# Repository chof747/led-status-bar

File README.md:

## Status bar with RGB Leds

This is a breakout board containing 5 WS2812B compatible RGB Leds that can be used to display some kind of status information or for other presentation stuff

It contains the following elements:

- 5 WS2812B compatible surface mount RGB leds
- MOSFETs acting as signal level shifters so it can be triggered by a 3V3 signal while the LEDs are powered by a higher voltage
- By-pass capacitors for each LED according to the data sheets
- A 4-pin header so that it can be connected to VDD (e.g. 5V) and VREF (e.g. 3v3), GND and a data line
  (1 - VDD, 2- Data, 3 - VREF, 4 - GND)
- It contains an outbound connector to daisy chain boards

## Revision History:

- **v1.0**: Initial version (filed for fabrication: 19.04.2023, assembled 14.5.2023)
- **v1.1**: Corrected revision including fixed version for level shifting and an outbound connector

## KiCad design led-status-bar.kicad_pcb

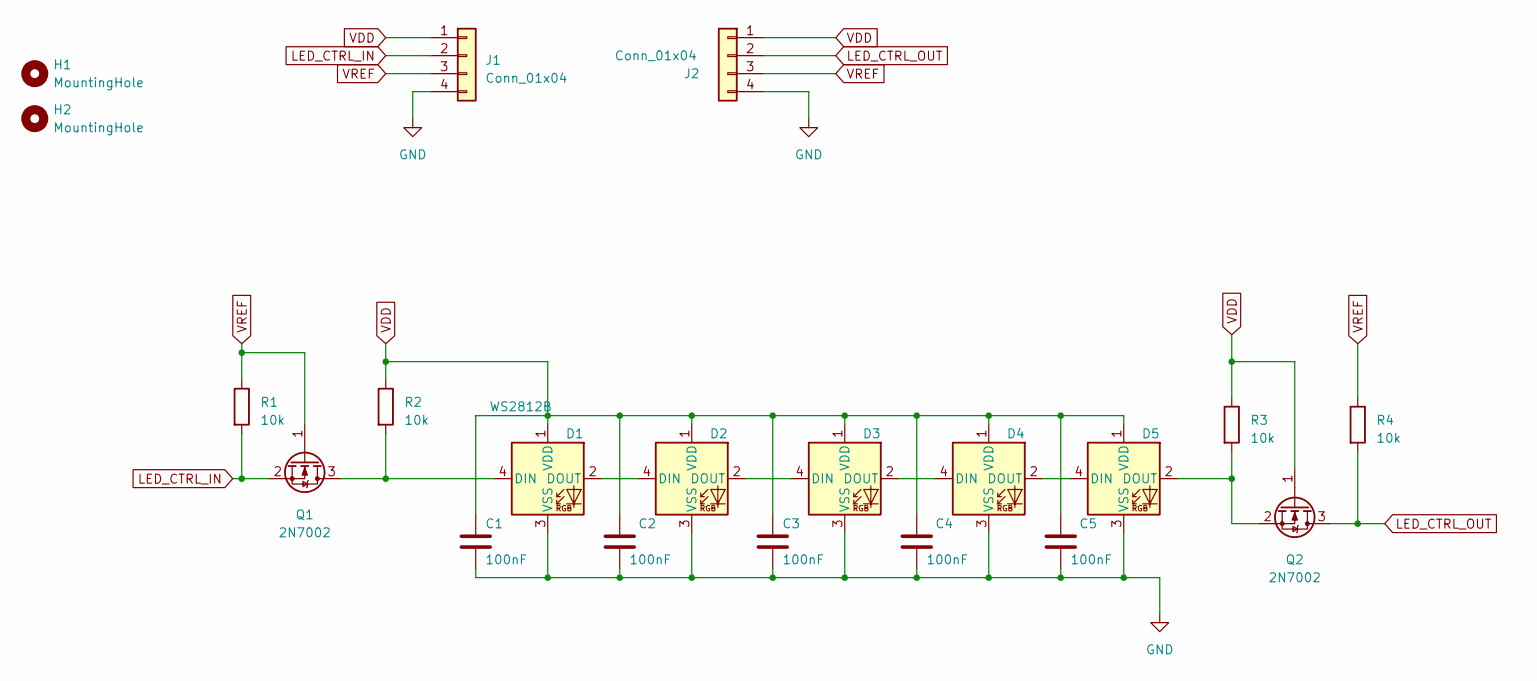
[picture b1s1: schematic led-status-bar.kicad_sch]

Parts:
C1, C2, C3, C4, C5: 100nF; C_0603_1608Metric_Pad1.08x0.95mm_HandSolder
D1, D2, D3, D4, D5: WS2812B; LED_WS2812B_PLCC4_5.0x5.0mm_P3.2mm
H1, H2: MountingHole; MountingHole_3.2mm_M3-smallBorder
J1: Conn_01x04; PinHeader_1x04_P2.54mm_Horizontal
J2: Conn_01x04; PinSocket_1x04_P2.54mm_Horizontal
Q1, Q2: 2N7002; SOT-23
R1, R2, R3, R4: 10k; R_0603_1608Metric_Pad0.98x0.95mm_HandSolder

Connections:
GND: C1.2, C2.2, C3.2, C4.2, C5.2, D1.3 (VSS), D2.3 (VSS), D3.3 (VSS), D4.3 (VSS), D5.3 (VSS), J1.4, J2.4
LED_CTRL_IN: J1.2, Q1.2 (S), R1.2
LED_CTRL_OUT: J2.2, Q2.3 (D), R4.2
unnamed: D1.4 (DIN), Q1.3 (D), R2.2
unnamed: D1.2 (DOUT), D2.4 (DIN)
unnamed: D2.2 (DOUT), D3.4 (DIN)
unnamed: D3.2 (DOUT), D4.4 (DIN)
unnamed: D4.2 (DOUT), D5.4 (DIN)
unnamed: D5.2 (DOUT), Q2.2 (S), R3.2
VDD: C1.1, C2.1, C3.1, C4.1, C5.1, D1.1 (VDD), D2.1 (VDD), D3.1 (VDD), D4.1 (VDD), D5.1 (VDD), J1.1, J2.1, Q2.1 (G), R2.1, R3.1
VREF: J1.3, J2.3, Q1.1 (G), R1.1, R4.1

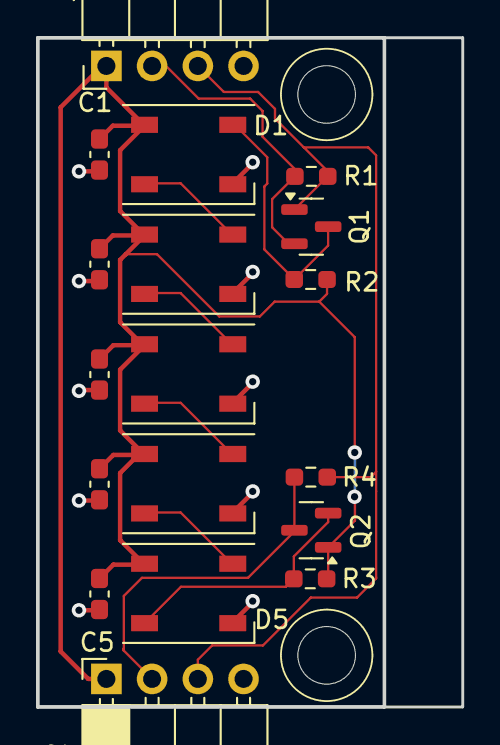
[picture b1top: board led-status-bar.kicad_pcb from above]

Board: 2 copper layers, 23.6 x 37.2 mm, 20 parts (0 on the bottom side), 11 nets.

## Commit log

2023-04-19 Initialization
2023-04-20 Revision 1 commit
    - Added all required connections to the PCB
    - Fabrication revision 1
    - Added README with suitable information
2023-04-20 Added pinout to back of board
2023-04-27 Updated template for KiCAD 7
2023-05-16 Revision 1.1 - Correcting error with Level shift
    - Changed BJTs with N-Channel Mosfets
    - Added resistors accordingly
    - Added an outbound connector
    - Added Vref (3v3) to allow daisy chaining
2023-05-16 Corrected fab descriptions of connectors
2023-05-31 Final version for rev. 1.1
2023-09-19 Minor change: replaced pin headers with angled ones
2024-03-14 upgrade to KiCad 8.0
2024-05-06 Changes of uids - done by KiCad
